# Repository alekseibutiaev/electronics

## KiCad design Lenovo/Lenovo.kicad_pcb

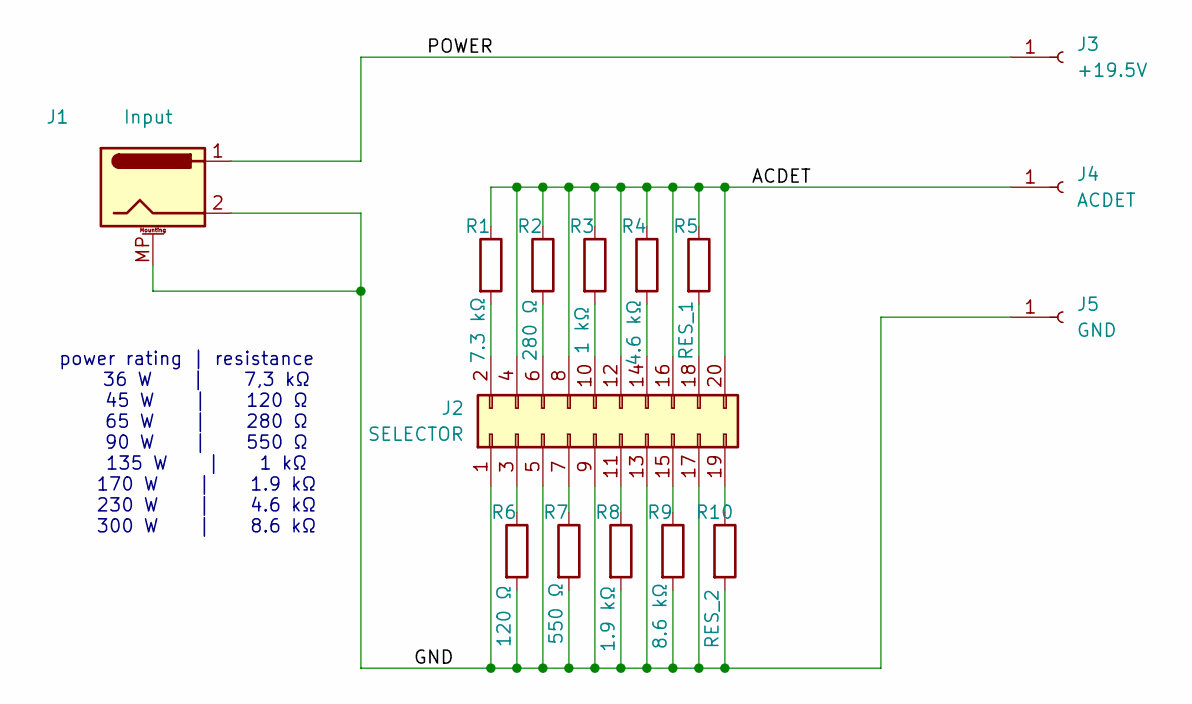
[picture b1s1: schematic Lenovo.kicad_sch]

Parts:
J1: Input; BarrelJack_DC007B; PARTREV A
J2: SELECTOR; PinHeader_2x10_P2.54mm_Vertical
J3: +19.5V; SolderWire-2sqmm_1x01_D2mm_OD3.9mm
J4: ACDET; SolderWire-0.5sqmm_1x01_D0.9mm_OD2.1mm
J5: GND; SolderWire-2sqmm_1x01_D2mm_OD3.9mm
R1: 7.3 kΩ; R_0805_2012Metric
R2: 280 Ω; R_0805_2012Metric
R3: 1 kΩ; R_0805_2012Metric
R4: 4.6 kΩ; R_0805_2012Metric
R5: RES_1; R_0805_2012Metric
R6: 120 Ω; R_0805_2012Metric
R7: 550 Ω; R_0805_2012Metric
R8: 1.9 kΩ; R_0805_2012Metric
R9: 8.6 kΩ; R_0805_2012Metric
R10: RES_2; R_0805_2012Metric

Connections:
/ACDET: J2.4, J2.8, J2.12, J2.16, J2.20, J4.1, R1.1, R2.1, R3.1, R4.1, R5.1
/GND: J1.2, J1.MP (MountPin), J2.1, J2.5, J2.9, J2.13, J2.17, J5.1, R6.2, R7.2, R8.2, R9.2, R10.2
/POWER: J1.1, J3.1
unnamed: J2.2, R1.2
unnamed: J2.3, R6.1
unnamed: J2.6, R2.2
unnamed: J2.7, R7.1
unnamed: J2.10, R3.2
unnamed: J2.11, R8.1
unnamed: J2.14, R4.2
unnamed: J2.15, R9.1
unnamed: J2.18, R5.2
unnamed: J2.19, R10.1

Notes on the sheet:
power rating | resistance 36 W | 7,3 kΩ 45 W | 120 Ω 65 W | 280 Ω 90 W | 550 Ω 135 W | 1 kΩ 170 W | 1.9 kΩ 230 W | 4.6 kΩ 300 W | 8.6 kΩ

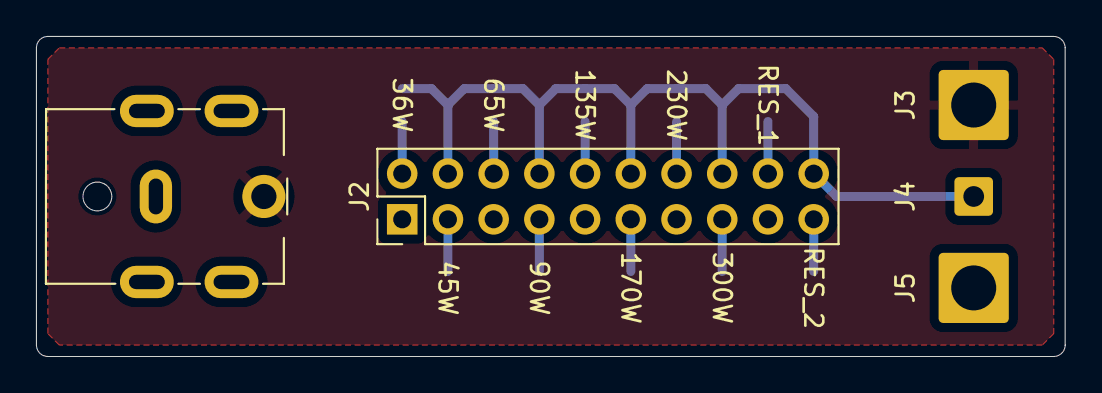
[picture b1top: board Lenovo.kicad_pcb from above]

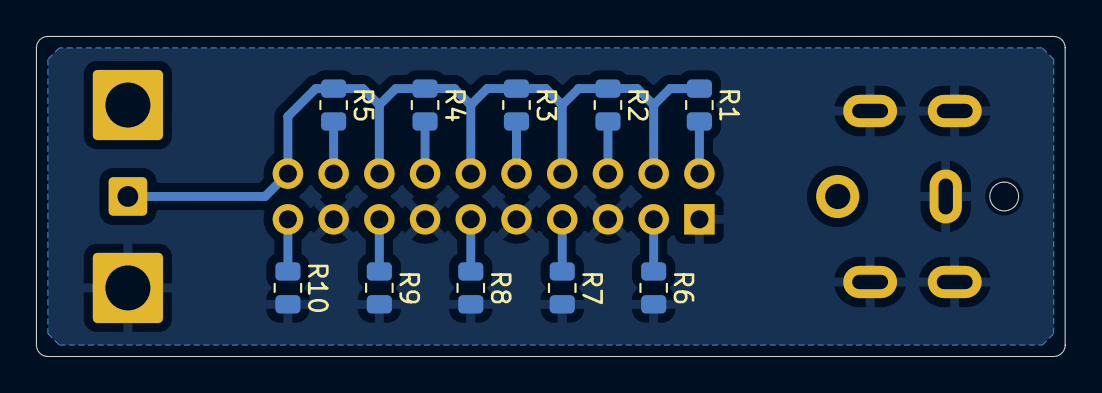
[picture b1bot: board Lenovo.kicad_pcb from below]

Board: 2 copper layers, 57.1 x 17.8 mm, 15 parts (10 on the bottom side), 13 nets.

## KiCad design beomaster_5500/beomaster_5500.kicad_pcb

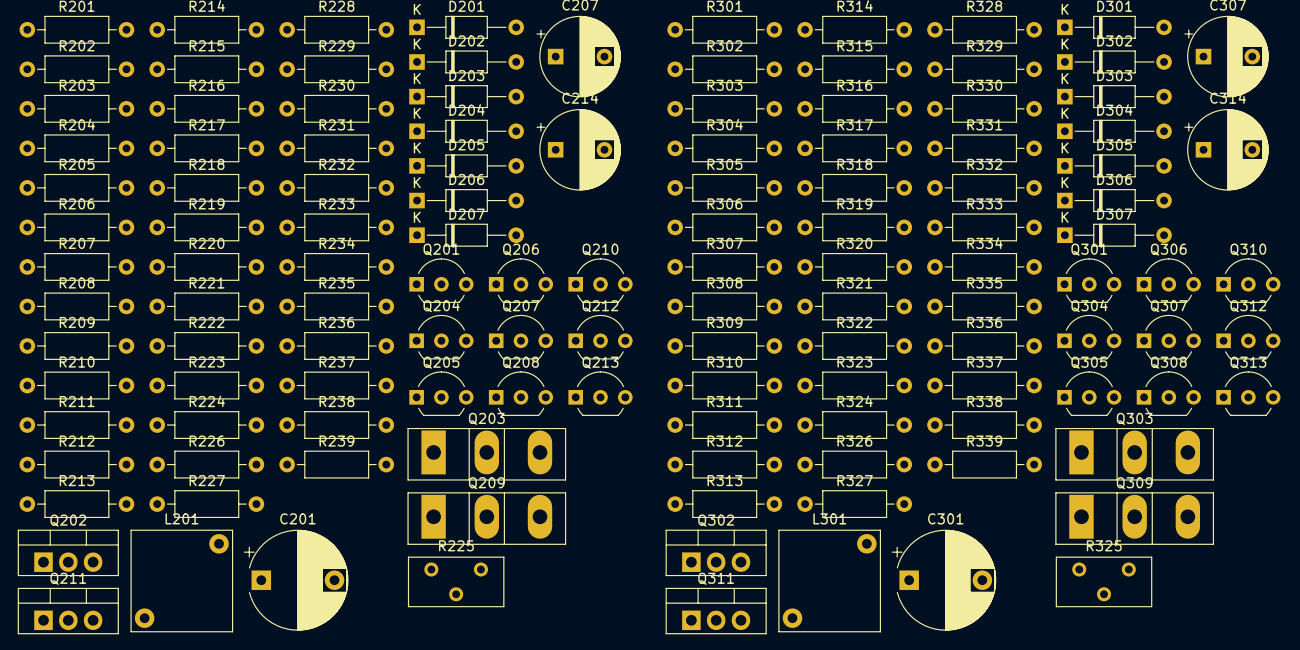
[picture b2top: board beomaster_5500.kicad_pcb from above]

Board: 2 copper layers, 126 parts (0 on the bottom side), 80 nets, no tracks yet.

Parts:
C201, C301: 100UFx50V; CP_Radial_D10.0mm_P7.50mm
C207, C307: 10UFx16V; CP_Radial_D8.0mm_P5.00mm
C214, C314: 100UFx10V; CP_Radial_D8.0mm_P5.00mm
D201, D202, D203, D204, D205, D206, D301, D302, D303, D304, D305, D306: 1N4148; D_DO-35_SOD27_P10.16mm_Horizontal
D207, D307: 12V; D_DO-35_SOD27_P10.16mm_Horizontal
L201, L301: 0,5UH; L_Radial_L10.2mm_W10.2mm_Px7.62mm_Py7.62mm_Pulse_LP-30
Q201, Q301: BF423; TO-92_Inline_Wide
Q202, Q211, Q302, Q311: BF857; TO-220-3_Vertical
Q203, Q303: BDV65B; TO-247-3_Vertical
Q204, Q206, Q207, Q210, Q213, Q304, Q306, Q307, Q310, Q313: BC547B; TO-92_Inline_Wide
Q205, Q305: BF422; TO-92_Inline_Wide
Q208, Q308: BC557B; TO-92_Inline_Wide
Q209, Q309: BDV64B; TO-247-3_Vertical
Q212, Q312: MPSA13; TO-92_Inline_Wide
R201, R301: 150; R_Axial_DIN0207_L6.3mm_D2.5mm_P10.16mm_Horizontal
R202, R203, R302, R303: 560; R_Axial_DIN0207_L6.3mm_D2.5mm_P10.16mm_Horizontal
R204, R239, R304, R339: 68; R_Axial_DIN0207_L6.3mm_D2.5mm_P10.16mm_Horizontal
R205, R305: 220K; R_Axial_DIN0207_L6.3mm_D2.5mm_P10.16mm_Horizontal
R206, R220, R221, R230, R306, R320, R321, R330: 1K; R_Axial_DIN0207_L6.3mm_D2.5mm_P10.16mm_Horizontal
R207, R307: 27; R_Axial_DIN0207_L6.3mm_D2.5mm_P10.16mm_Horizontal
R208, R308: 2,2M; R_Axial_DIN0207_L6.3mm_D2.5mm_P10.16mm_Horizontal
R209, R214, R219, R222, R223, R227, R309, R314, R319, R322, R323, R327: 10K; R_Axial_DIN0207_L6.3mm_D2.5mm_P10.16mm_Horizontal
R210, R216, R310, R316: 2,2K; R_Axial_DIN0207_L6.3mm_D2.5mm_P10.16mm_Horizontal
R211, R311: 680; R_Axial_DIN0207_L6.3mm_D2.5mm_P10.16mm_Horizontal
R212, R229, R238, R312, R329, R338: 270; R_Axial_DIN0207_L6.3mm_D2.5mm_P10.16mm_Horizontal
R213, R313: 33K; R_Axial_DIN0207_L6.3mm_D2.5mm_P10.16mm_Horizontal
R215, R315: 470; R_Axial_DIN0207_L6.3mm_D2.5mm_P10.16mm_Horizontal
R217, R224, R317, R324: 390; R_Axial_DIN0207_L6.3mm_D2.5mm_P10.16mm_Horizontal
R218, R226, R318, R326: 0.22; R_Axial_DIN0207_L6.3mm_D2.5mm_P10.16mm_Horizontal
R225, R325: 100; Potentiometer_Bourns_3296Y_Vertical
R228, R231, R328, R331: 100; R_Axial_DIN0207_L6.3mm_D2.5mm_P10.16mm_Horizontal
R232, R233, R332, R333: 15K; R_Axial_DIN0207_L6.3mm_D2.5mm_P10.16mm_Horizontal
R234, R334: 3,3K; R_Axial_DIN0207_L6.3mm_D2.5mm_P10.16mm_Horizontal
R235, R335: 47; R_Axial_DIN0207_L6.3mm_D2.5mm_P10.16mm_Horizontal
R236, R336: 4,7; R_Axial_DIN0207_L6.3mm_D2.5mm_P10.16mm_Horizontal
R237, R337: 180; R_Axial_DIN0207_L6.3mm_D2.5mm_P10.16mm_Horizontal

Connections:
/Left Channel/+40V: Q202.2 (C), Q203.3 (C), R201.2, R205.1, R206.1
/Left Channel/-40V: C214.2, D207.2 (A), Q209.2 (C), Q213.1 (E), R237.2, R238.1, R239.2
/Left Channel/OUT: L201.1, R218.2, R226.1
/Right Channel/+40V: Q302.2 (C), Q303.3 (C), R301.2, R305.1, R306.1
/Right Channel/-40V: C314.2, D307.2 (A), Q309.2 (C), Q313.1 (E), R337.2, R338.1, R339.2
/Right Channel/OUT: L301.1, R318.2, R326.1
GND: C201.2, C301.2, D204.1 (K), D205.1 (K), D304.1 (K), D305.1 (K), R228.2, R234.1, R236.2, R328.2, R334.1, R336.2
GND1: R210.1, R223.2, R228.1, R310.1, R323.2, R328.1
unnamed: C201.1, R201.1, R202.1, R203.1, R204.1
unnamed: R202.2, R207.1
unnamed: R221.2, R223.1
unnamed: C301.1, R301.1, R302.1, R303.1, R304.1
unnamed: R302.2, R307.1
unnamed: R321.2, R323.1
unnamed: D201.2 (A), R205.2, R208.1
unnamed: D201.1 (K), R206.2
unnamed: D202.2 (A), Q201.3 (E)
unnamed: D202.1 (K), D203.2 (A), Q202.3 (B), R211.1
unnamed: D203.1 (K), Q204.3 (C)
unnamed: D204.2 (A), R214.1
unnamed: D205.2 (A), R227.1
unnamed: D206.2 (A), Q208.1 (E)
unnamed: D206.1 (K), R231.1
unnamed: D207.1 (K), R232.1, R233.2, R234.2
unnamed: D301.2 (A), R305.2, R308.1
unnamed: D301.1 (K), R306.2
unnamed: D302.2 (A), Q301.3 (E)
unnamed: D302.1 (K), D303.2 (A), Q302.3 (B), R311.1
unnamed: D303.1 (K), Q304.3 (C)
unnamed: D304.2 (A), R314.1
unnamed: D305.2 (A), R327.1
unnamed: D306.2 (A), Q308.1 (E)
unnamed: D306.1 (K), R331.1
unnamed: D307.1 (K), R332.1, R333.2, R334.2
unnamed: Q201.1 (B), Q206.3 (C), R207.2
unnamed: Q201.2 (C), R204.2
unnamed: Q202.1 (E), Q203.2 (B), R211.2, R216.1, R217.1
unnamed: Q203.1 (E), R212.2, R213.1, R218.1
unnamed: Q204.2 (B), R212.1, R214.2
unnamed: Q204.1 (E), Q208.3 (C), R222.1
unnamed: C207.1, Q205.2 (B), R208.2, R213.2, R215.1
unnamed: Q205.3 (C), R209.2
unnamed: C207.2, Q205.1 (E), Q209.1 (E), R215.2, R226.2, R229.2
unnamed: Q206.2 (B), R221.1
unnamed: Q206.1 (E), Q207.1 (E), R230.2
unnamed: Q207.2 (B), R219.2, R222.2, R224.2
unnamed: Q207.3 (C), R203.2
unnamed: Q208.2 (B), R227.2, R229.1
unnamed: Q209.3 (B), Q211.2 (C), R225.2, R225.3, R231.2
unnamed: Q210.2 (B), Q213.3 (C), R232.2
unnamed: Q210.3 (C), R230.1
unnamed: Q210.1 (E), Q213.2 (B), R238.2
unnamed: C214.1, Q211.3 (B), Q212.3 (C), R233.1
unnamed: Q211.1 (E), R235.1, R237.1
unnamed: Q212.2 (B), R235.2
unnamed: Q212.1 (E), R239.1
unnamed: Q301.1 (B), Q306.3 (C), R307.2
unnamed: Q301.2 (C), R304.2
unnamed: Q302.1 (E), Q303.2 (B), R311.2, R316.1, R317.1
unnamed: Q303.1 (E), R312.2, R313.1, R318.1
unnamed: Q304.2 (B), R312.1, R314.2
unnamed: Q304.1 (E), Q308.3 (C), R322.1
unnamed: C307.1, Q305.2 (B), R308.2, R313.2, R315.1
unnamed: Q305.3 (C), R309.2
unnamed: C307.2, Q305.1 (E), Q309.1 (E), R315.2, R326.2, R329.2
unnamed: Q306.2 (B), R321.1
unnamed: Q306.1 (E), Q307.1 (E), R330.2
unnamed: Q307.2 (B), R319.2, R322.2, R324.2
unnamed: Q307.3 (C), R303.2
unnamed: Q308.2 (B), R327.2, R329.1
unnamed: Q309.3 (B), Q311.2 (C), R325.2, R325.3, R331.2
unnamed: Q310.2 (B), Q313.3 (C), R332.2
unnamed: Q310.3 (C), R330.1
unnamed: Q310.1 (E), Q313.2 (B), R338.2
unnamed: C314.1, Q311.3 (B), Q312.3 (C), R333.1
unnamed: Q311.1 (E), R335.1, R337.1
unnamed: Q312.2 (B), R335.2
unnamed: Q312.1 (E), R339.1
unnamed: R216.2, R217.2, R225.1
unnamed: R316.2, R317.2, R325.1

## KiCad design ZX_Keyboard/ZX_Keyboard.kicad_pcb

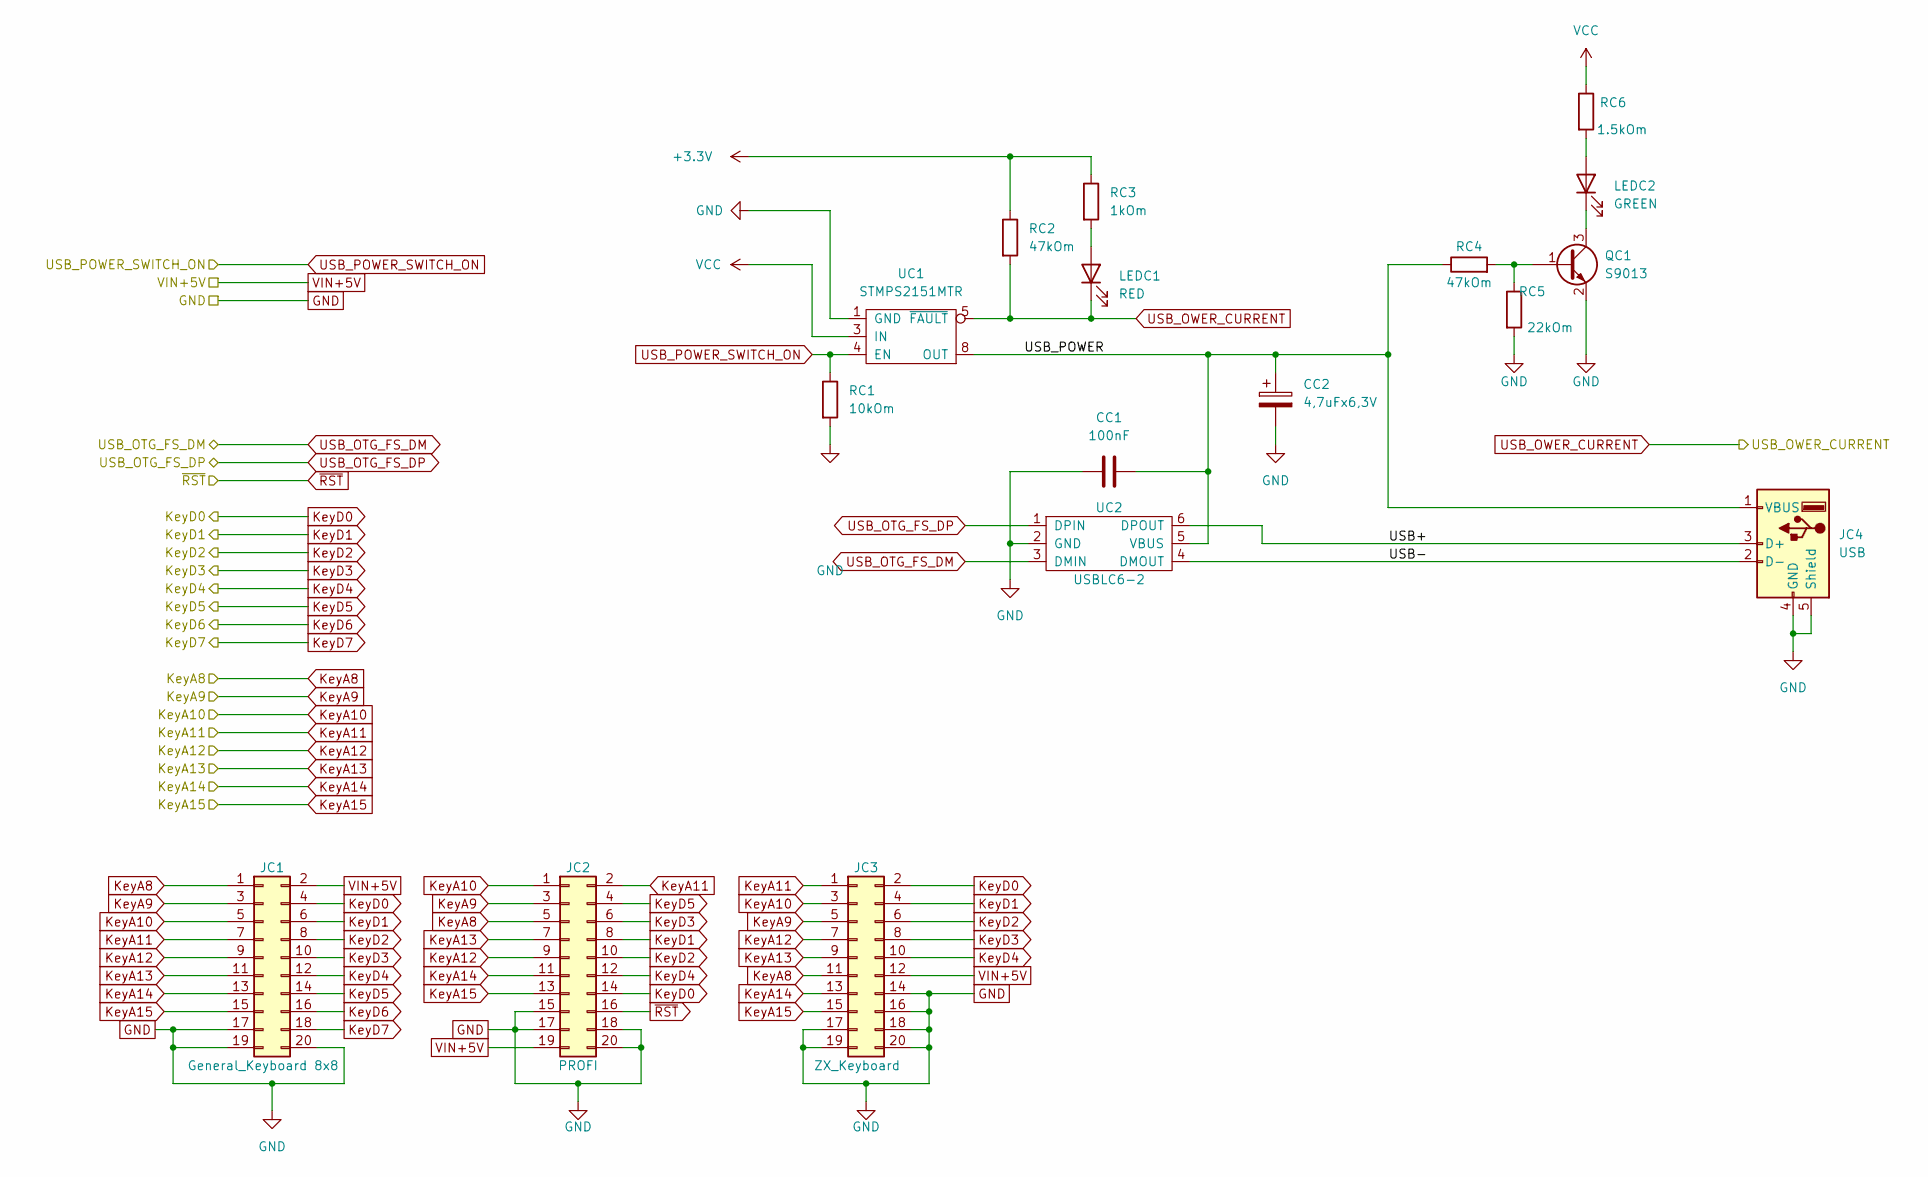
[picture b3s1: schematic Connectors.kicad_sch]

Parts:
CC1: 100nF; C_0805_2012Metric_Pad1.18x1.45mm_HandSolder
CC2: 4,7uFx6,3V; CP_EIA-3216-18_Kemet-A_Pad1.58x1.35mm_HandSolder
JC1: General_Keyboard 8x8; PinHeader_2x10_P2.54mm_Vertical
JC2: PROFI; PinHeader_2x10_P2.54mm_Vertical
JC3: ZX_Keyboard; PinHeader_2x10_P2.54mm_Vertical
JC4: USB; USB_A_Molex_67643_Horizontal
LEDC1: RED; LED_0805_2012Metric_Pad1.15x1.40mm_HandSolder
LEDC2: GREEN; LED_0805_2012Metric_Pad1.15x1.40mm_HandSolder
QC1: S9013; SOT-23_Handsoldering
RC1: 10kOm; R_0805_2012Metric_Pad1.20x1.40mm_HandSolder
RC2, RC4: 47kOm; R_0805_2012Metric_Pad1.20x1.40mm_HandSolder
RC3: 1kOm; R_0805_2012Metric_Pad1.20x1.40mm_HandSolder
RC5: 22kOm; R_0805_2012Metric_Pad1.20x1.40mm_HandSolder
RC6: 1.5kOm; R_0805_2012Metric_Pad1.20x1.40mm_HandSolder
UC1: STMPS2151MTR; SO-8_3.9x4.9mm_P1.27mm
UC2: USBLC6-2; SOT-23-6_Handsoldering

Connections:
+3.3V: RC2.1, RC3.1; also elsewhere on the board
/Connectors/USB+: JC4.3 (D+), UC2.6 (DPOUT)
/Connectors/USB-: JC4.2 (D-), UC2.4 (DMOUT)
/Connectors/USB_POWER: CC1.2, CC2.1, JC4.1 (VBUS), RC4.1, UC1.6 (OUT), UC1.7 (OUT), UC1.8 (OUT), UC2.5 (VBUS)
GND: CC1.1, CC2.2, JC1.17, JC1.19, JC1.20, JC2.15, JC2.17, JC2.18, JC2.20, JC3.14, JC3.16, JC3.17, JC3.18, JC3.19, JC3.20, JC4.4 (GND), JC4.5 (Shield), QC1.2 (E), RC1.2, RC5.2, UC1.1 (GND), UC2.2 (GND); also elsewhere on the board
KeyA8: JC1.1, JC2.5, JC3.11; also elsewhere on the board
KeyA9: JC1.3, JC2.3, JC3.5; also elsewhere on the board
KeyA10: JC1.5, JC2.1, JC3.3; also elsewhere on the board
KeyA11: JC1.7, JC2.2, JC3.1; also elsewhere on the board
KeyA12: JC1.9, JC2.9, JC3.7; also elsewhere on the board
KeyA13: JC1.11, JC2.7, JC3.9; also elsewhere on the board
KeyA14: JC1.13, JC2.11, JC3.13; also elsewhere on the board
KeyA15: JC1.15, JC2.13, JC3.15; also elsewhere on the board
KeyD0: JC1.4, JC2.14, JC3.2; also elsewhere on the board
KeyD1: JC1.6, JC2.8, JC3.4; also elsewhere on the board
KeyD2: JC1.8, JC2.10, JC3.6; also elsewhere on the board
KeyD3: JC1.10, JC2.6, JC3.8; also elsewhere on the board
KeyD4: JC1.12, JC2.12, JC3.10; also elsewhere on the board
KeyD5: JC1.14, JC2.4; also elsewhere on the board
KeyD6: JC1.16; also elsewhere on the board
KeyD7: JC1.18; also elsewhere on the board
unnamed: LEDC1.2 (A), RC3.2
unnamed: LEDC2.2 (A), RC6.2
unnamed: LEDC2.1 (K), QC1.3 (C)
unnamed: QC1.1 (B), RC4.2, RC5.1
USB_OTG_FS_DM: UC2.3 (DMIN); also elsewhere on the board
USB_OTG_FS_DP: UC2.1 (DPIN); also elsewhere on the board
USB_OWER_CURRENT: LEDC1.1 (K), RC2.2, UC1.5 (~FAULT); also elsewhere on the board
USB_POWER_SWITCH_ON: RC1.1, UC1.4 (EN); also elsewhere on the board
VCC: RC6.1, UC1.2 (IN), UC1.3 (IN); also elsewhere on the board
VIN+5V: JC1.2, JC2.19, JC3.12; also elsewhere on the board
~RST: JC2.16; also elsewhere on the board

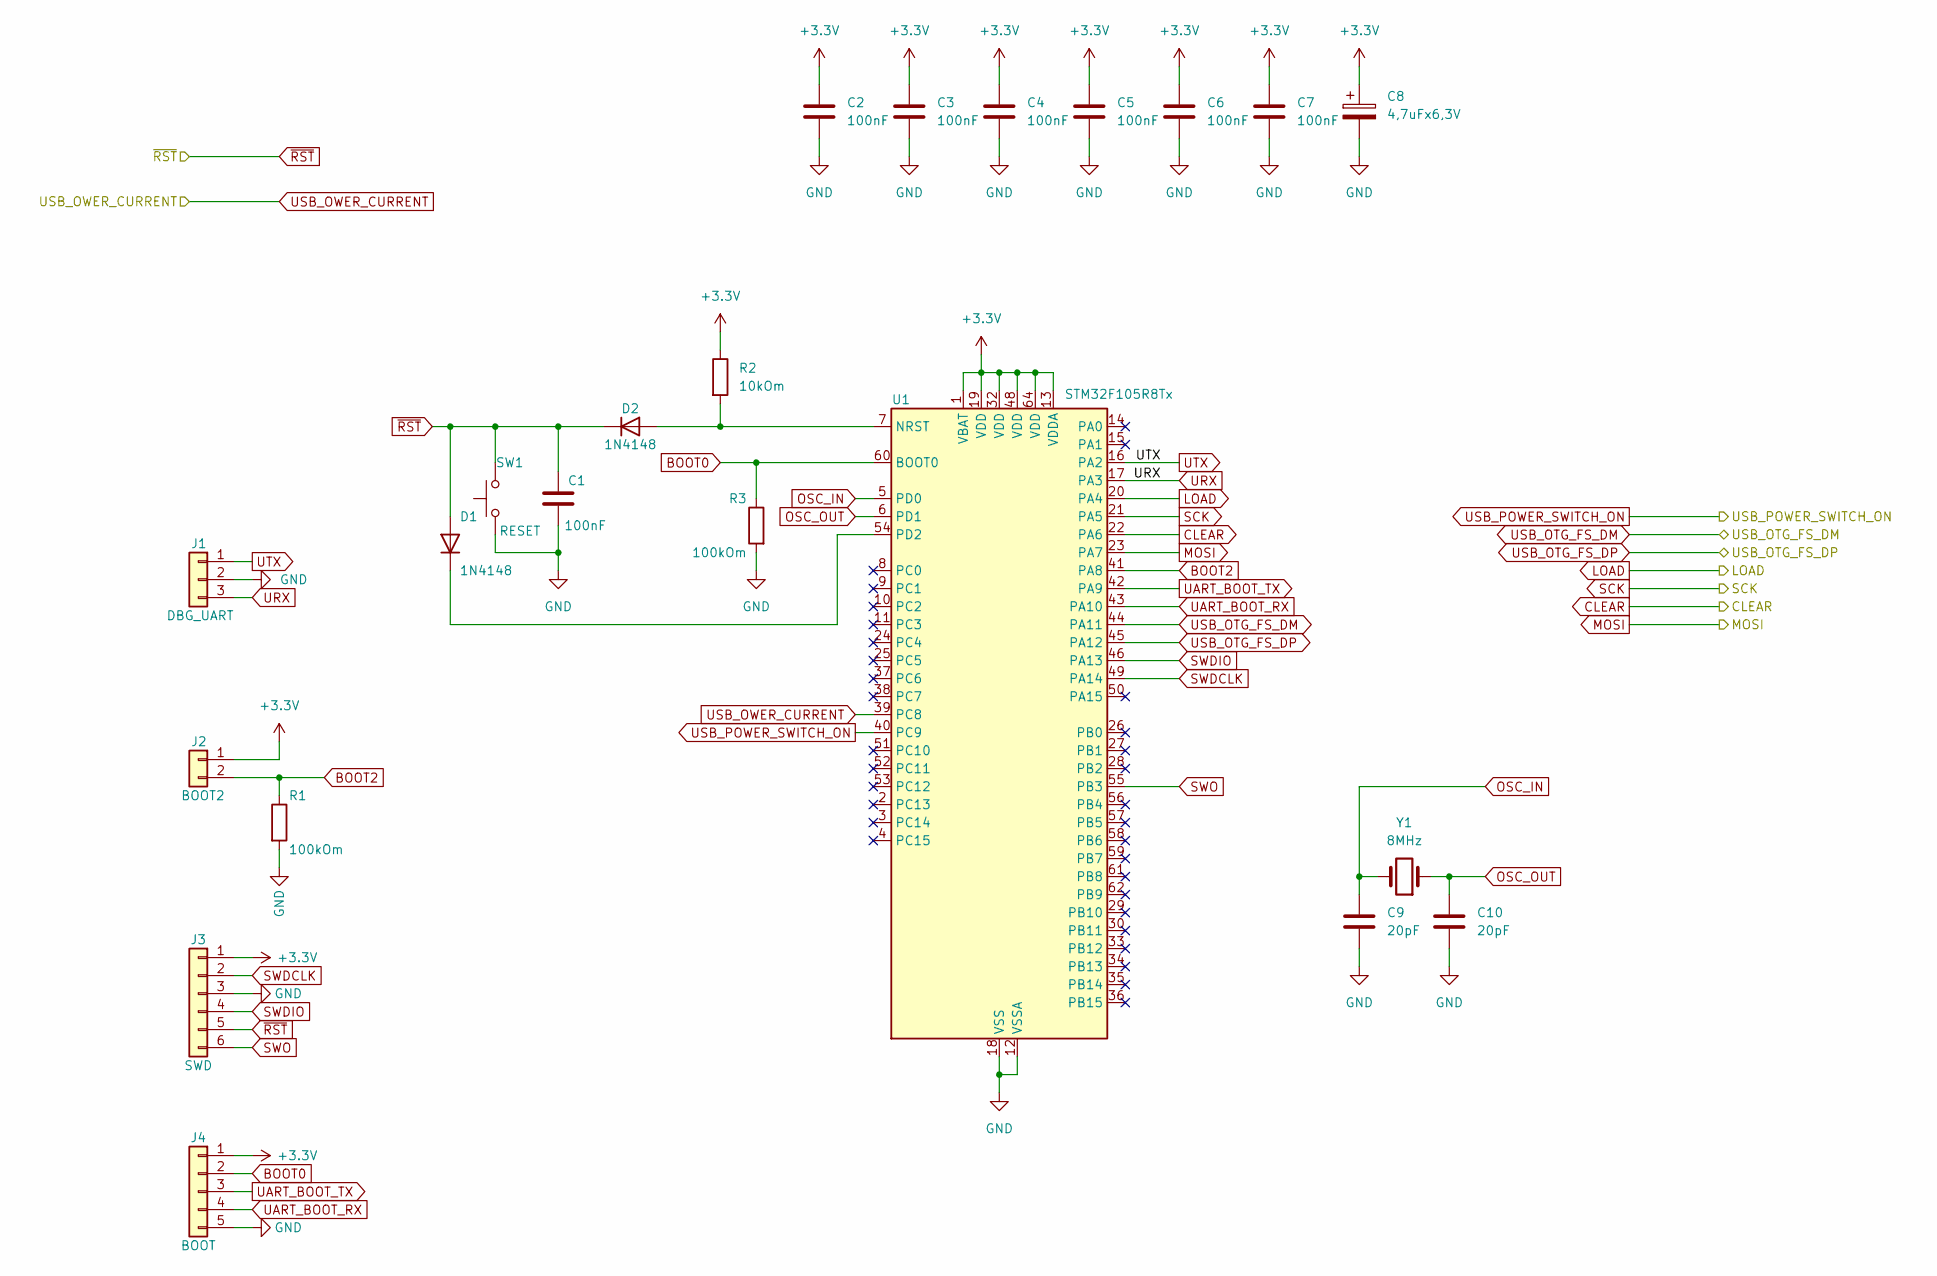
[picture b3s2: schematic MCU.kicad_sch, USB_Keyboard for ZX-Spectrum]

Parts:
C1, C2, C3, C4, C5, C6, C7: 100nF; C_0805_2012Metric_Pad1.18x1.45mm_HandSolder
C8: 4,7uFx6,3V; CP_EIA-3216-18_Kemet-A_Pad1.58x1.35mm_HandSolder
C9, C10: 20pF; C_0805_2012Metric_Pad1.18x1.45mm_HandSolder
D1, D2: 1N4148; D_MiniMELF
J1: DBG_UART; PinHeader_1x03_P2.54mm_Vertical
J2: BOOT2; PinHeader_1x02_P2.54mm_Vertical
J3: SWD; PinHeader_1x06_P2.54mm_Vertical
J4: BOOT; PinHeader_1x05_P2.54mm_Vertical
R1, R3: 100kOm; R_0805_2012Metric_Pad1.20x1.40mm_HandSolder
R2: 10kOm; R_0805_2012Metric_Pad1.20x1.40mm_HandSolder
SW1: RESET; SW_PUSH_6mm
U1: STM32F105R8Tx; LQFP-64_10x10mm_P0.5mm
Y1: 8MHz; Crystal_HC49-U_Vertical

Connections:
+3.3V: C2.1, C3.1, C4.1, C5.1, C6.1, C7.1, C8.1, J2.1, J3.1, J4.1, R2.1, U1.1 (VBAT), U1.13 (VDDA), U1.19 (VDD), U1.32 (VDD), U1.48 (VDD), U1.64 (VDD); also elsewhere on the board
BOOT0: J4.2, R3.1, U1.60 (BOOT0)
BOOT2: J2.2, R1.1, U1.41 (PA8)
CLEAR: U1.22 (PA6); also elsewhere on the board
GND: C1.2, C2.2, C3.2, C4.2, C5.2, C6.2, C7.2, C8.2, C9.2, C10.2, J1.2, J3.3, J4.5, R1.2, R3.2, SW1.1, U1.12 (VSSA), U1.18 (VSS), U1.31 (VSS), U1.47 (VSS), U1.63 (VSS); also elsewhere on the board
LOAD: U1.20 (PA4); also elsewhere on the board
MOSI: U1.23 (PA7); also elsewhere on the board
unnamed: D1.1 (K), U1.54 (PD2)
unnamed: D2.2 (A), R2.2, U1.7 (NRST)
OSC_IN: C9.1, U1.5 (PD0), Y1.2
OSC_OUT: C10.1, U1.6 (PD1), Y1.1
SCK: U1.21 (PA5); also elsewhere on the board
SWDCLK: J3.2, U1.49 (PA14)
SWDIO: J3.4, U1.46 (PA13)
SWO: J3.6, U1.55 (PB3)
UART_BOOT_RX: J4.4, U1.43 (PA10)
UART_BOOT_TX: J4.3, U1.42 (PA9)
URX: J1.3, U1.17 (PA3)
USB_OTG_FS_DM: U1.44 (PA11); also elsewhere on the board
USB_OTG_FS_DP: U1.45 (PA12); also elsewhere on the board
USB_OWER_CURRENT: U1.39 (PC8); also elsewhere on the board
USB_POWER_SWITCH_ON: U1.40 (PC9); also elsewhere on the board
UTX: J1.1, U1.16 (PA2)
~RST: C1.1, D1.2 (A), D2.1 (K), J3.5, SW1.2; also elsewhere on the board

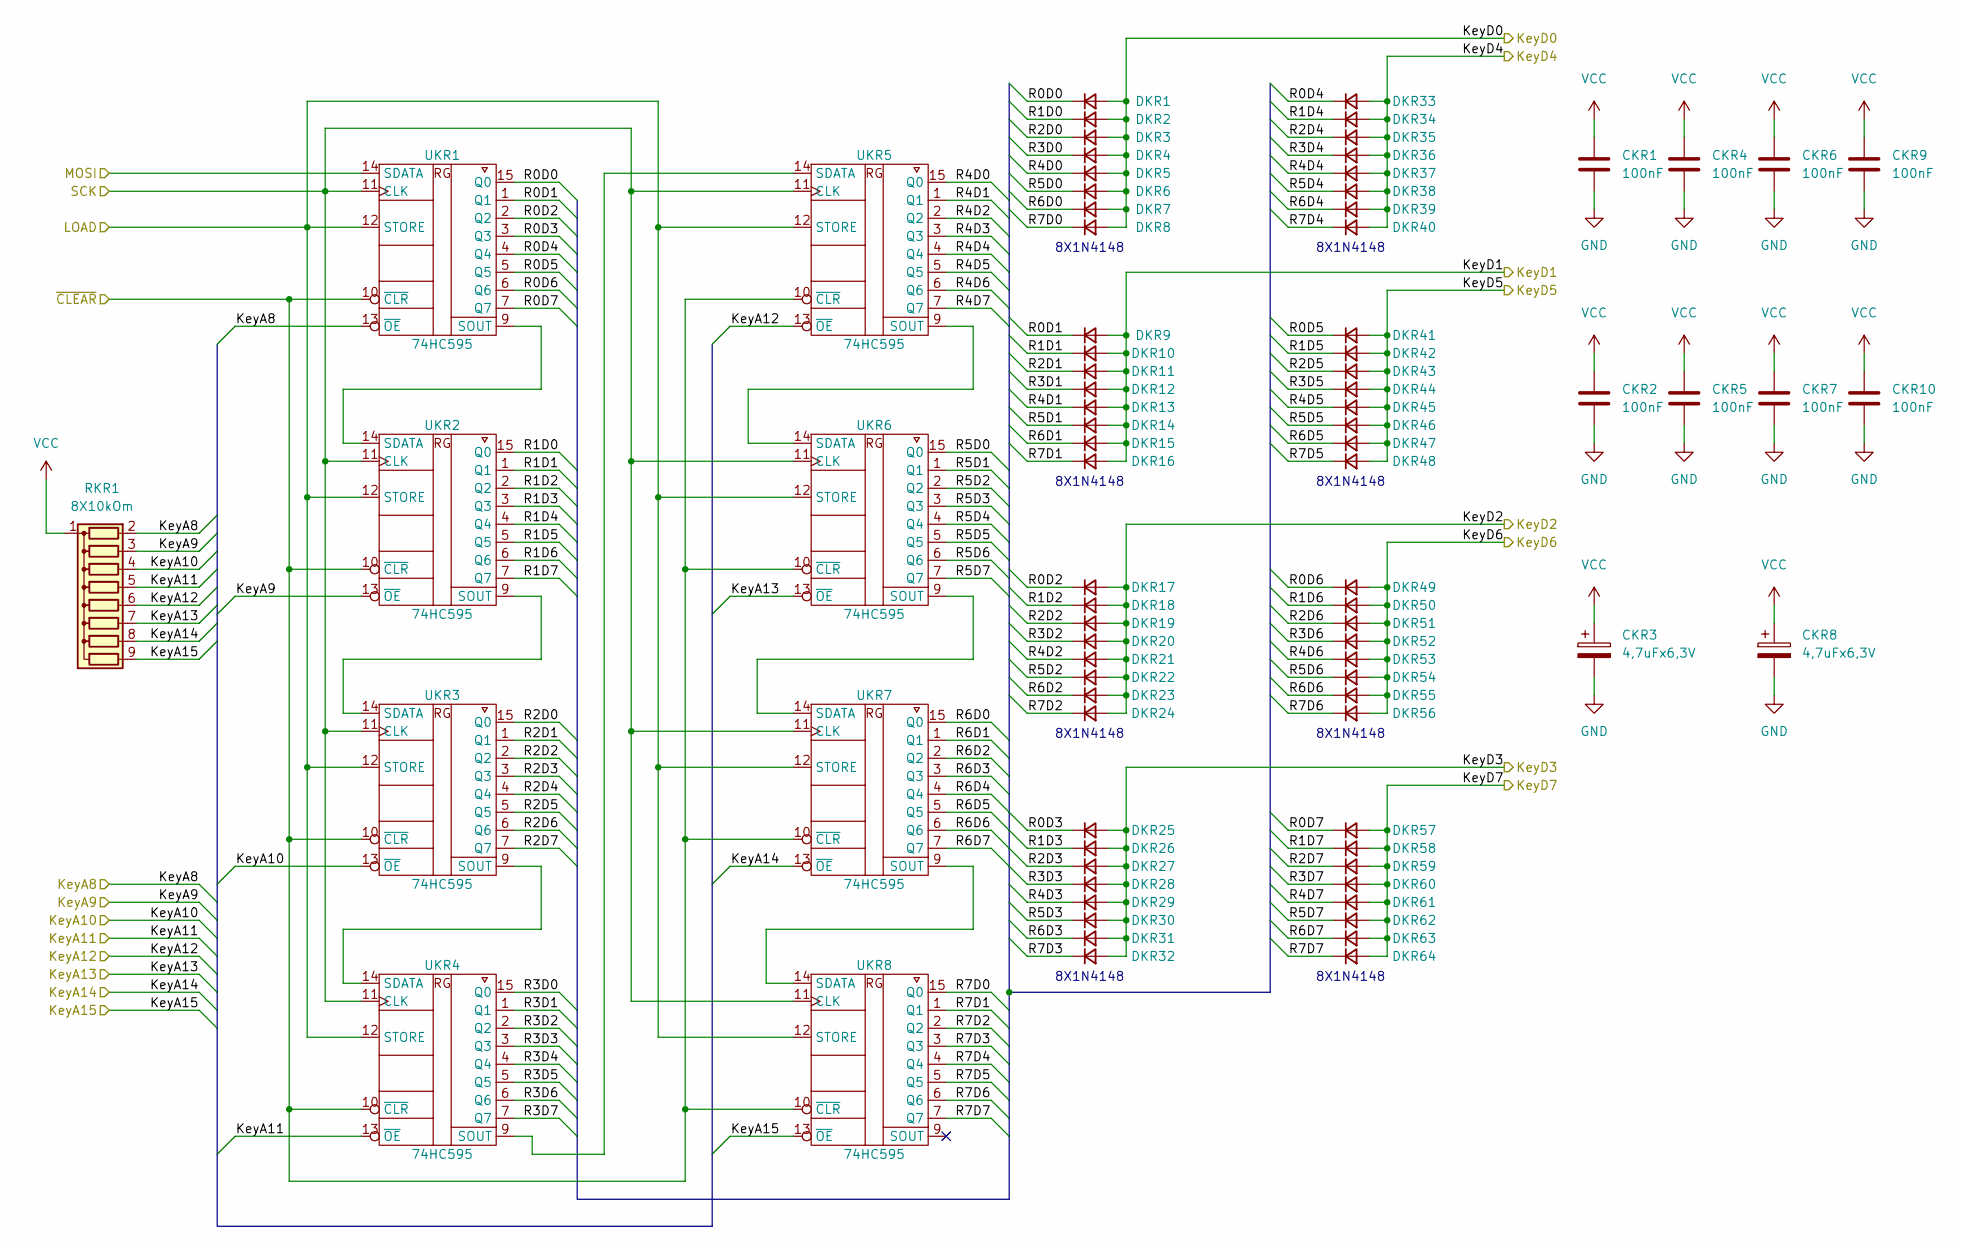
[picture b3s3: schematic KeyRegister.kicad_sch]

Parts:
CKR1, CKR2, CKR4, CKR5, CKR6, CKR7, CKR9, CKR10: 100nF; C_0805_2012Metric_Pad1.18x1.45mm_HandSolder
CKR3, CKR8: 4,7uFx6,3V; CP_EIA-3216-18_Kemet-A_Pad1.58x1.35mm_HandSolder
DKR1, DKR2, DKR3, DKR4, DKR5, DKR6, DKR7, DKR8, DKR9, DKR10, DKR11, DKR12, DKR13, DKR14, DKR15, DKR16, DKR17, DKR18, DKR19, DKR20, DKR21, DKR22, DKR23, DKR24, DKR25, DKR26, DKR27, DKR28, DKR29, DKR30, DKR31, DKR32, DKR33, DKR34, DKR35, DKR36, DKR37, DKR38, DKR39, DKR40, DKR41, DKR42, DKR43, DKR44, DKR45, DKR46, DKR47, DKR48, DKR49, DKR50, DKR51, DKR52, DKR53, DKR54, DKR55, DKR56, DKR57, DKR58, DKR59, DKR60, DKR61, DKR62, DKR63, DKR64: 1N4148; D_MiniMELF
RKR1: 8X10kOm; R_Array_SIP9
UKR1, UKR2, UKR3, UKR4, UKR5, UKR6, UKR7, UKR8: 74HC595; SO-16_5.3x10.2mm_P1.27mm

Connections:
/KeyRegister/R0D0: DKR1.1 (K), UKR1.15 (Q0)
/KeyRegister/R0D1: DKR9.1 (K), UKR1.1 (Q1)
/KeyRegister/R0D2: DKR17.1 (K), UKR1.2 (Q2)
/KeyRegister/R0D3: DKR25.1 (K), UKR1.3 (Q3)
/KeyRegister/R0D4: DKR33.1 (K), UKR1.4 (Q4)
/KeyRegister/R0D5: DKR41.1 (K), UKR1.5 (Q5)
/KeyRegister/R0D6: DKR49.1 (K), UKR1.6 (Q6)
/KeyRegister/R0D7: DKR57.1 (K), UKR1.7 (Q7)
/KeyRegister/R1D0: DKR2.1 (K), UKR2.15 (Q0)
/KeyRegister/R1D1: DKR10.1 (K), UKR2.1 (Q1)
/KeyRegister/R1D2: DKR18.1 (K), UKR2.2 (Q2)
/KeyRegister/R1D3: DKR26.1 (K), UKR2.3 (Q3)
/KeyRegister/R1D4: DKR34.1 (K), UKR2.4 (Q4)
/KeyRegister/R1D5: DKR42.1 (K), UKR2.5 (Q5)
/KeyRegister/R1D6: DKR50.1 (K), UKR2.6 (Q6)
/KeyRegister/R1D7: DKR58.1 (K), UKR2.7 (Q7)
/KeyRegister/R2D0: DKR3.1 (K), UKR3.15 (Q0)
/KeyRegister/R2D1: DKR11.1 (K), UKR3.1 (Q1)
/KeyRegister/R2D2: DKR19.1 (K), UKR3.2 (Q2)
/KeyRegister/R2D3: DKR27.1 (K), UKR3.3 (Q3)
/KeyRegister/R2D4: DKR35.1 (K), UKR3.4 (Q4)
/KeyRegister/R2D5: DKR43.1 (K), UKR3.5 (Q5)
/KeyRegister/R2D6: DKR51.1 (K), UKR3.6 (Q6)
/KeyRegister/R2D7: DKR59.1 (K), UKR3.7 (Q7)
/KeyRegister/R3D0: DKR4.1 (K), UKR4.15 (Q0)
/KeyRegister/R3D1: DKR12.1 (K), UKR4.1 (Q1)
/KeyRegister/R3D2: DKR20.1 (K), UKR4.2 (Q2)
/KeyRegister/R3D3: DKR28.1 (K), UKR4.3 (Q3)
/KeyRegister/R3D4: DKR36.1 (K), UKR4.4 (Q4)
/KeyRegister/R3D5: DKR44.1 (K), UKR4.5 (Q5)
/KeyRegister/R3D6: DKR52.1 (K), UKR4.6 (Q6)
/KeyRegister/R3D7: DKR60.1 (K), UKR4.7 (Q7)
/KeyRegister/R4D0: DKR5.1 (K), UKR5.15 (Q0)
/KeyRegister/R4D1: DKR13.1 (K), UKR5.1 (Q1)
/KeyRegister/R4D2: DKR21.1 (K), UKR5.2 (Q2)
/KeyRegister/R4D3: DKR29.1 (K), UKR5.3 (Q3)
/KeyRegister/R4D4: DKR37.1 (K), UKR5.4 (Q4)
/KeyRegister/R4D5: DKR45.1 (K), UKR5.5 (Q5)
/KeyRegister/R4D6: DKR53.1 (K), UKR5.6 (Q6)
/KeyRegister/R4D7: DKR61.1 (K), UKR5.7 (Q7)
/KeyRegister/R5D0: DKR6.1 (K), UKR6.15 (Q0)
/KeyRegister/R5D1: DKR14.1 (K), UKR6.1 (Q1)
/KeyRegister/R5D2: DKR22.1 (K), UKR6.2 (Q2)
/KeyRegister/R5D3: DKR30.1 (K), UKR6.3 (Q3)
/KeyRegister/R5D4: DKR38.1 (K), UKR6.4 (Q4)
/KeyRegister/R5D5: DKR46.1 (K), UKR6.5 (Q5)
/KeyRegister/R5D6: DKR54.1 (K), UKR6.6 (Q6)
/KeyRegister/R5D7: DKR62.1 (K), UKR6.7 (Q7)
/KeyRegister/R6D0: DKR7.1 (K), UKR7.15 (Q0)
/KeyRegister/R6D1: DKR15.1 (K), UKR7.1 (Q1)
/KeyRegister/R6D2: DKR23.1 (K), UKR7.2 (Q2)
/KeyRegister/R6D3: DKR31.1 (K), UKR7.3 (Q3)
/KeyRegister/R6D4: DKR39.1 (K), UKR7.4 (Q4)
/KeyRegister/R6D5: DKR47.1 (K), UKR7.5 (Q5)
/KeyRegister/R6D6: DKR55.1 (K), UKR7.6 (Q6)
/KeyRegister/R6D7: DKR63.1 (K), UKR7.7 (Q7)
/KeyRegister/R7D0: DKR8.1 (K), UKR8.15 (Q0)
/KeyRegister/R7D1: DKR16.1 (K), UKR8.1 (Q1)
/KeyRegister/R7D2: DKR24.1 (K), UKR8.2 (Q2)
/KeyRegister/R7D3: DKR32.1 (K), UKR8.3 (Q3)
/KeyRegister/R7D4: DKR40.1 (K), UKR8.4 (Q4)
/KeyRegister/R7D5: DKR48.1 (K), UKR8.5 (Q5)
/KeyRegister/R7D6: DKR56.1 (K), UKR8.6 (Q6)
/KeyRegister/R7D7: DKR64.1 (K), UKR8.7 (Q7)
CLEAR: UKR1.10 (~CLR), UKR2.10 (~CLR), UKR3.10 (~CLR), UKR4.10 (~CLR), UKR5.10 (~CLR), UKR6.10 (~CLR), UKR7.10 (~CLR), UKR8.10 (~CLR); also elsewhere on the board
GND: CKR1.2, CKR2.2, CKR3.2, CKR4.2, CKR5.2, CKR6.2, CKR7.2, CKR8.2, CKR9.2, CKR10.2, UKR1.8 (GND), UKR2.8 (GND), UKR3.8 (GND), UKR4.8 (GND), UKR5.8 (GND), UKR6.8 (GND), UKR7.8 (GND), UKR8.8 (GND); also elsewhere on the board
KeyA8: RKR1.2 (R1), UKR1.13 (~OE); also elsewhere on the board
KeyA9: RKR1.3 (R2), UKR2.13 (~OE); also elsewhere on the board
KeyA10: RKR1.4 (R3), UKR3.13 (~OE); also elsewhere on the board
KeyA11: RKR1.5 (R4), UKR4.13 (~OE); also elsewhere on the board
KeyA12: RKR1.6 (R5), UKR5.13 (~OE); also elsewhere on the board
KeyA13: RKR1.7 (R6), UKR6.13 (~OE); also elsewhere on the board
KeyA14: RKR1.8 (R7), UKR7.13 (~OE); also elsewhere on the board
KeyA15: RKR1.9 (R8), UKR8.13 (~OE); also elsewhere on the board
KeyD0: DKR1.2 (A), DKR2.2 (A), DKR3.2 (A), DKR4.2 (A), DKR5.2 (A), DKR6.2 (A), DKR7.2 (A), DKR8.2 (A); also elsewhere on the board
KeyD1: DKR9.2 (A), DKR10.2 (A), DKR11.2 (A), DKR12.2 (A), DKR13.2 (A), DKR14.2 (A), DKR15.2 (A), DKR16.2 (A); also elsewhere on the board
KeyD2: DKR17.2 (A), DKR18.2 (A), DKR19.2 (A), DKR20.2 (A), DKR21.2 (A), DKR22.2 (A), DKR23.2 (A), DKR24.2 (A); also elsewhere on the board
KeyD3: DKR25.2 (A), DKR26.2 (A), DKR27.2 (A), DKR28.2 (A), DKR29.2 (A), DKR30.2 (A), DKR31.2 (A), DKR32.2 (A); also elsewhere on the board
KeyD4: DKR33.2 (A), DKR34.2 (A), DKR35.2 (A), DKR36.2 (A), DKR37.2 (A), DKR38.2 (A), DKR39.2 (A), DKR40.2 (A); also elsewhere on the board
KeyD5: DKR41.2 (A), DKR42.2 (A), DKR43.2 (A), DKR44.2 (A), DKR45.2 (A), DKR46.2 (A), DKR47.2 (A), DKR48.2 (A); also elsewhere on the board
KeyD6: DKR49.2 (A), DKR50.2 (A), DKR51.2 (A), DKR52.2 (A), DKR53.2 (A), DKR54.2 (A), DKR55.2 (A), DKR56.2 (A); also elsewhere on the board
KeyD7: DKR57.2 (A), DKR58.2 (A), DKR59.2 (A), DKR60.2 (A), DKR61.2 (A), DKR62.2 (A), DKR63.2 (A), DKR64.2 (A); also elsewhere on the board
LOAD: UKR1.12 (STORE), UKR2.12 (STORE), UKR3.12 (STORE), UKR4.12 (STORE), UKR5.12 (STORE), UKR6.12 (STORE), UKR7.12 (STORE), UKR8.12 (STORE); also elsewhere on the board
MOSI: UKR1.14 (SDATA); also elsewhere on the board
unnamed: UKR1.9 (SOUT), UKR2.14 (SDATA)
unnamed: UKR2.9 (SOUT), UKR3.14 (SDATA)
unnamed: UKR3.9 (SOUT), UKR4.14 (SDATA)
unnamed: UKR4.9 (SOUT), UKR5.14 (SDATA)
unnamed: UKR5.9 (SOUT), UKR6.14 (SDATA)
unnamed: UKR6.9 (SOUT), UKR7.14 (SDATA)
unnamed: UKR7.9 (SOUT), UKR8.14 (SDATA)
SCK: UKR1.11 (CLK), UKR2.11 (CLK), UKR3.11 (CLK), UKR4.11 (CLK), UKR5.11 (CLK), UKR6.11 (CLK), UKR7.11 (CLK), UKR8.11 (CLK); also elsewhere on the board
VCC: CKR1.1, CKR2.1, CKR3.1, CKR4.1, CKR5.1, CKR6.1, CKR7.1, CKR8.1, CKR9.1, CKR10.1, RKR1.1 (common), UKR1.16 (VCC), UKR2.16 (VCC), UKR3.16 (VCC), UKR4.16 (VCC), UKR5.16 (VCC), UKR6.16 (VCC), UKR7.16 (VCC), UKR8.16 (VCC); also elsewhere on the board

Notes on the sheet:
8X1N4148

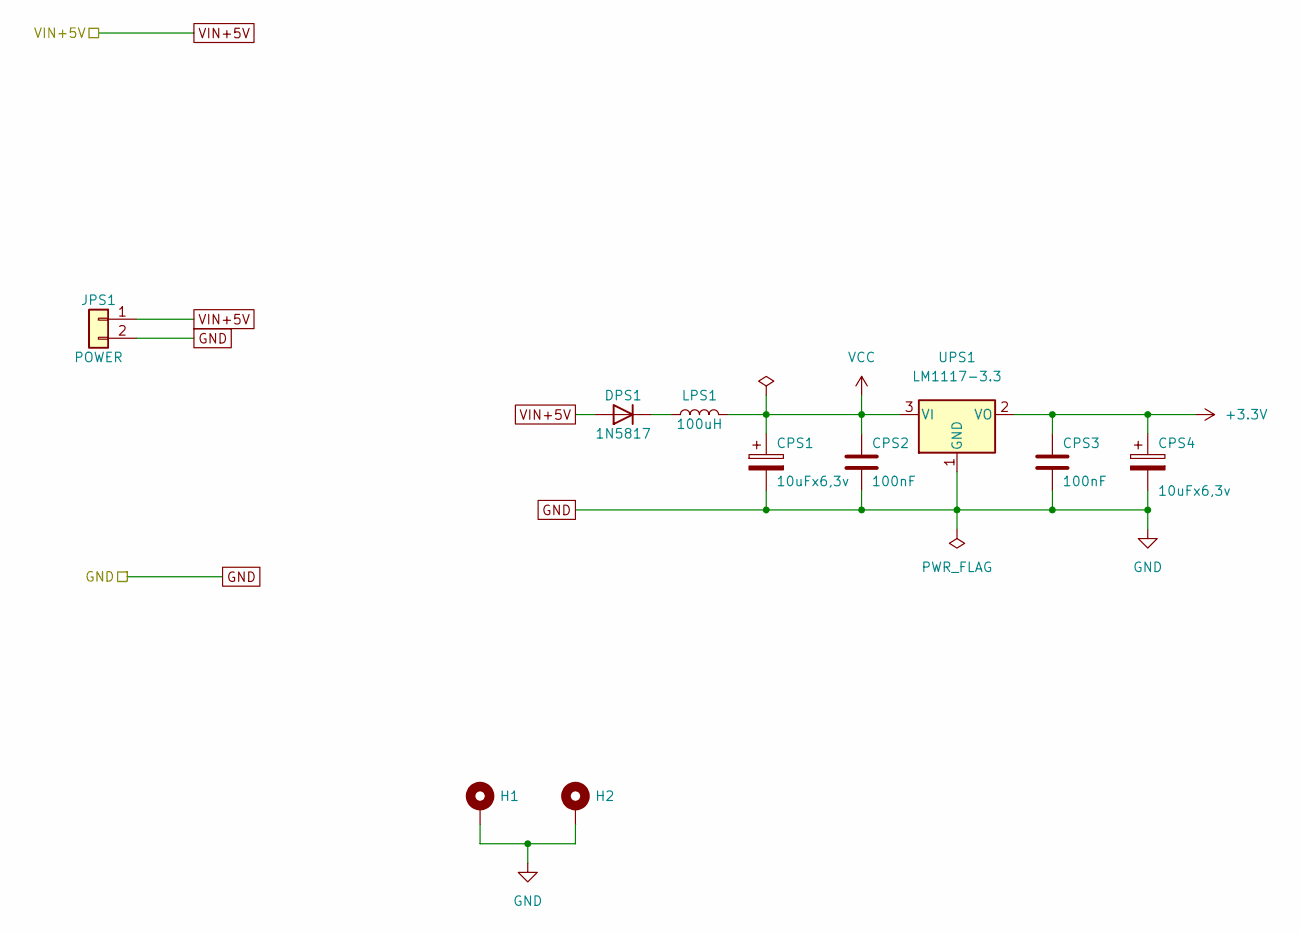
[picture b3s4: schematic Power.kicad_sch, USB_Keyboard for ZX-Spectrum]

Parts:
CPS1, CPS4: 10uFx6,3v; CP_EIA-3216-18_Kemet-A_Pad1.58x1.35mm_HandSolder
CPS2, CPS3: 100nF; C_0805_2012Metric_Pad1.18x1.45mm_HandSolder
DPS1: 1N5817; D_SMA
H1, H2: MountingHole_Pad; MountingHole_2.2mm_M2_Pad_Via
JPS1: POWER; PinHeader_1x02_P2.54mm_Vertical
LPS1: 100uH; CD43
UPS1: LM1117-3.3; SOT-223-3_TabPin2

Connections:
+3.3V: CPS3.1, CPS4.1, UPS1.2 (VO); also elsewhere on the board
GND: CPS1.2, CPS2.2, CPS3.2, CPS4.2, H1.1, H2.1, JPS1.2, UPS1.1 (GND); also elsewhere on the board
unnamed: DPS1.1 (K), LPS1.1
VCC: CPS1.1, CPS2.1, LPS1.2, UPS1.3 (VI); also elsewhere on the board
VIN+5V: DPS1.2 (A), JPS1.1; also elsewhere on the board
